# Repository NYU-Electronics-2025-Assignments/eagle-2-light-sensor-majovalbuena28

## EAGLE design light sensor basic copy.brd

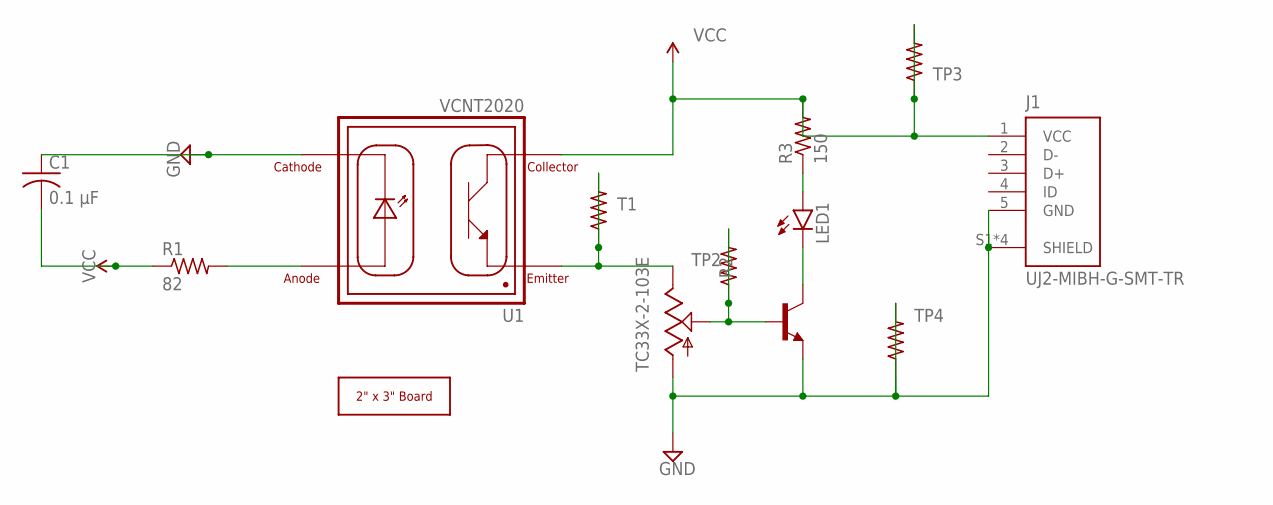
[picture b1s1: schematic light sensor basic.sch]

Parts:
C1: 0.1 µF; C0805
J1: UJ2-MIBH-G-SMT-TR; CUI_UJ2-MIBH-G-SMT-TR
LED1: LEDSML0805; SML0805
R1: 82; R0805
R2: TC33X-2-103E; SMD_TRIMM
R3: 150; R0805
R4, R5: R-US_M1206; M1206
R6, R7: R-US_R0805; R0805
T1: -NPN-SOT23-EBC; SOT23-EBC
U1: VCNT2020; XDCR_VCNT2020
U$1: 2X3_BOARD_V2

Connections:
GND: C1.1, U1.4 (CATHODE)
unnamed: R1.2, U1.3 (ANODE)
unnamed: LED1.C, T1.C
unnamed: R2.2, R7.1, R7.2, T1.B
unnamed: LED1.A, R3.1
TP2: R2.1, R6.1, R6.2, U1.1 (EMITTER)
TP3: J1.1 (VCC), R3.2, R5.1, R5.2, U1.2 (COLLECTOR)
TP4: J1.5 (GND), J1.S1 (SHIELD), J1.S2 (SHIELD), J1.S3 (SHIELD), J1.S4 (SHIELD), R2.3, R4.1, R4.2, T1.E
VCC: C1.2, R1.1

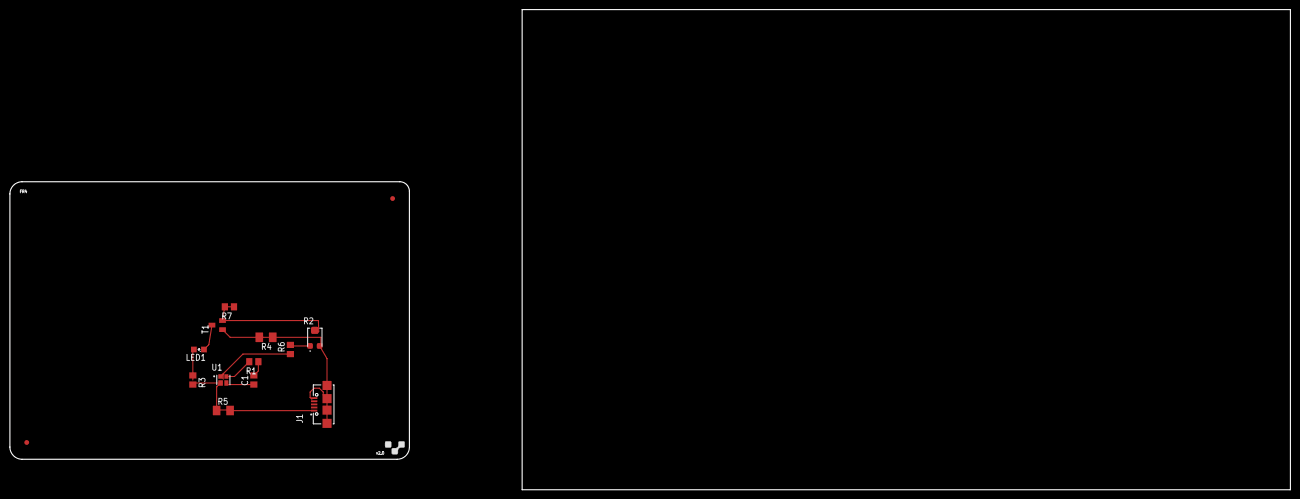
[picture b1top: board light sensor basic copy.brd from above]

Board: 2 copper layers, 83.2 x 57.8 mm, 13 parts (0 on the bottom side), 9 nets.

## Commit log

2025-05-03 board and cam
    board and cam for eagle 2

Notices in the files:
parts and their libraries:
SparkFun-PowerSymbols: Licensing: Creative Commons ShareAlike 4.0 International - https://creativecommons.org/licenses/by-sa/4.0
